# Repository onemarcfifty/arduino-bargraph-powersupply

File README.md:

# Episode8
fixed voltage power supply with Arduino bar graph display for current measurement

Find all details on [my youtube channel](https://www.youtube.com/channel/UCG5Ph9Mm6UEQLJJ-kGIC2AQ)

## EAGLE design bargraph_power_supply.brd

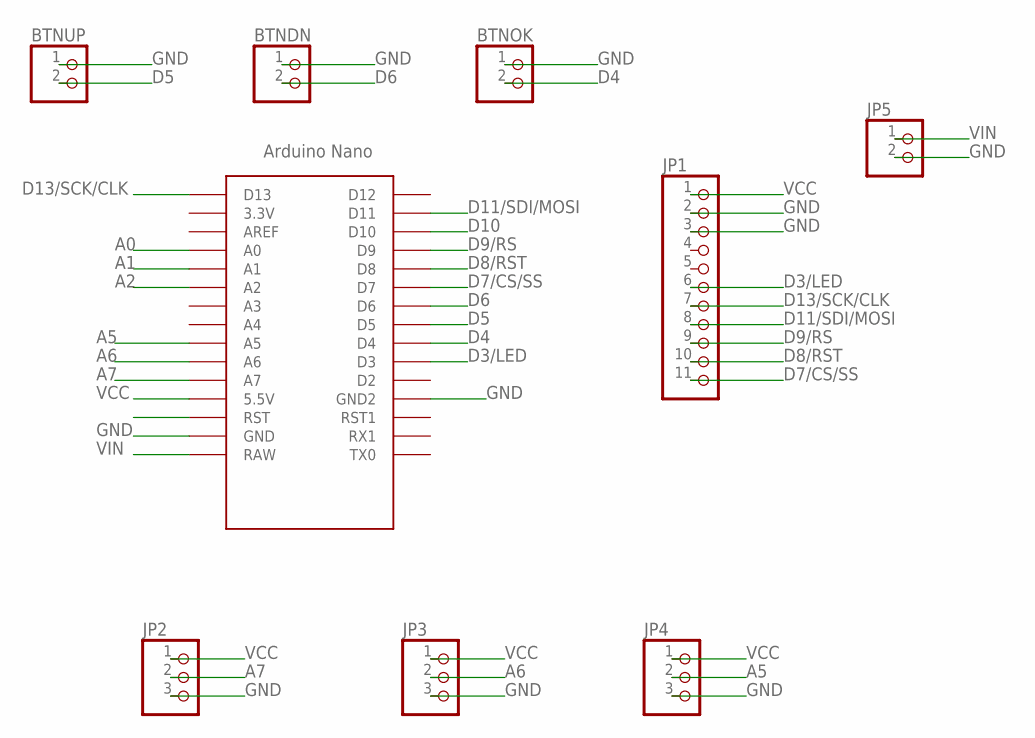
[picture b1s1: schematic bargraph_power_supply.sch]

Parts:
BTNDN: PINHD-1X2; 1X02
BTNOK: PINHD-1X2; 1X02
BTNUP: PINHD-1X2; 1X02
JP1: PINHD-1X11; 1X11
JP2, JP3, JP4: PINHD-1X3; 1X03
JP5: PINHD-1X2; 1X02
U$1: NANO

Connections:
A0: U$1.A0
A1: U$1.A1
A2: U$1.A2
A5: JP4.2, U$1.A5
A6: JP3.2, U$1.A6
A7: JP2.2, U$1.A7
D3/LED: JP1.6, U$1.D3
D4: BTNOK.2, U$1.D4
D5: BTNUP.2, U$1.D5
D6: BTNDN.2, U$1.D6
D7/CS/SS: JP1.11, U$1.D7
D8/RST: JP1.10, U$1.D8
D9/RS: JP1.9, U$1.D9
D10: U$1.D10
D11/SDI/MOSI: JP1.8, U$1.D11
D13/SCK/CLK: JP1.7, U$1.D13
GND: BTNDN.1, BTNOK.1, BTNUP.1, JP1.2, JP1.3, JP2.3, JP3.3, JP4.3, JP5.2, U$1.GND, U$1.GND1 (GND2)
VCC: JP1.1, JP2.1, JP3.1, JP4.1, U$1.5V (5.5V)
VIN: JP5.1, U$1.RAW

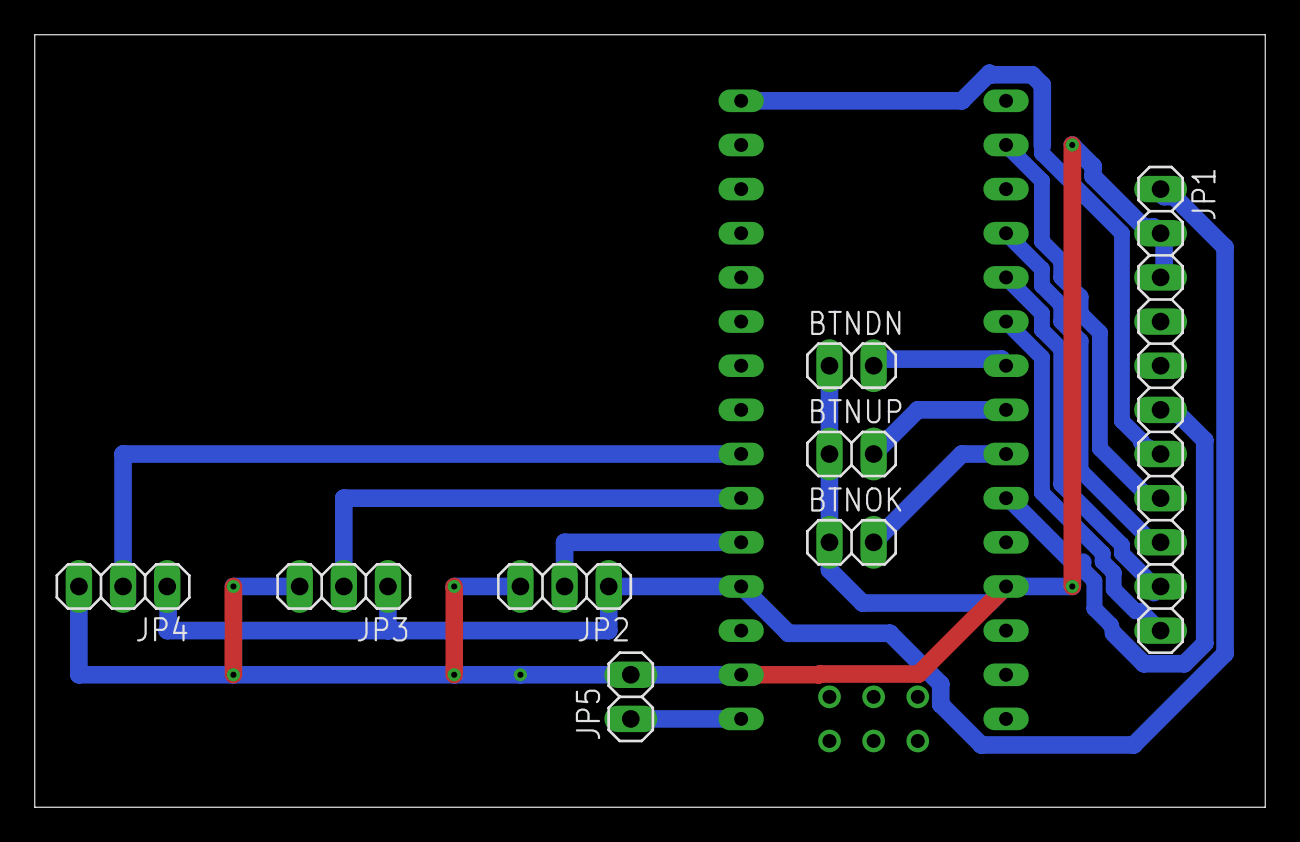
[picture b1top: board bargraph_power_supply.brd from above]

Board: 2 copper layers, 70.8 x 44.4 mm, 9 parts (0 on the bottom side), 15 nets.

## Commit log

2020-03-21 Arduino sketch uploaded
2020-03-21 Added photo
2020-03-22 Added EAGLE schematics
